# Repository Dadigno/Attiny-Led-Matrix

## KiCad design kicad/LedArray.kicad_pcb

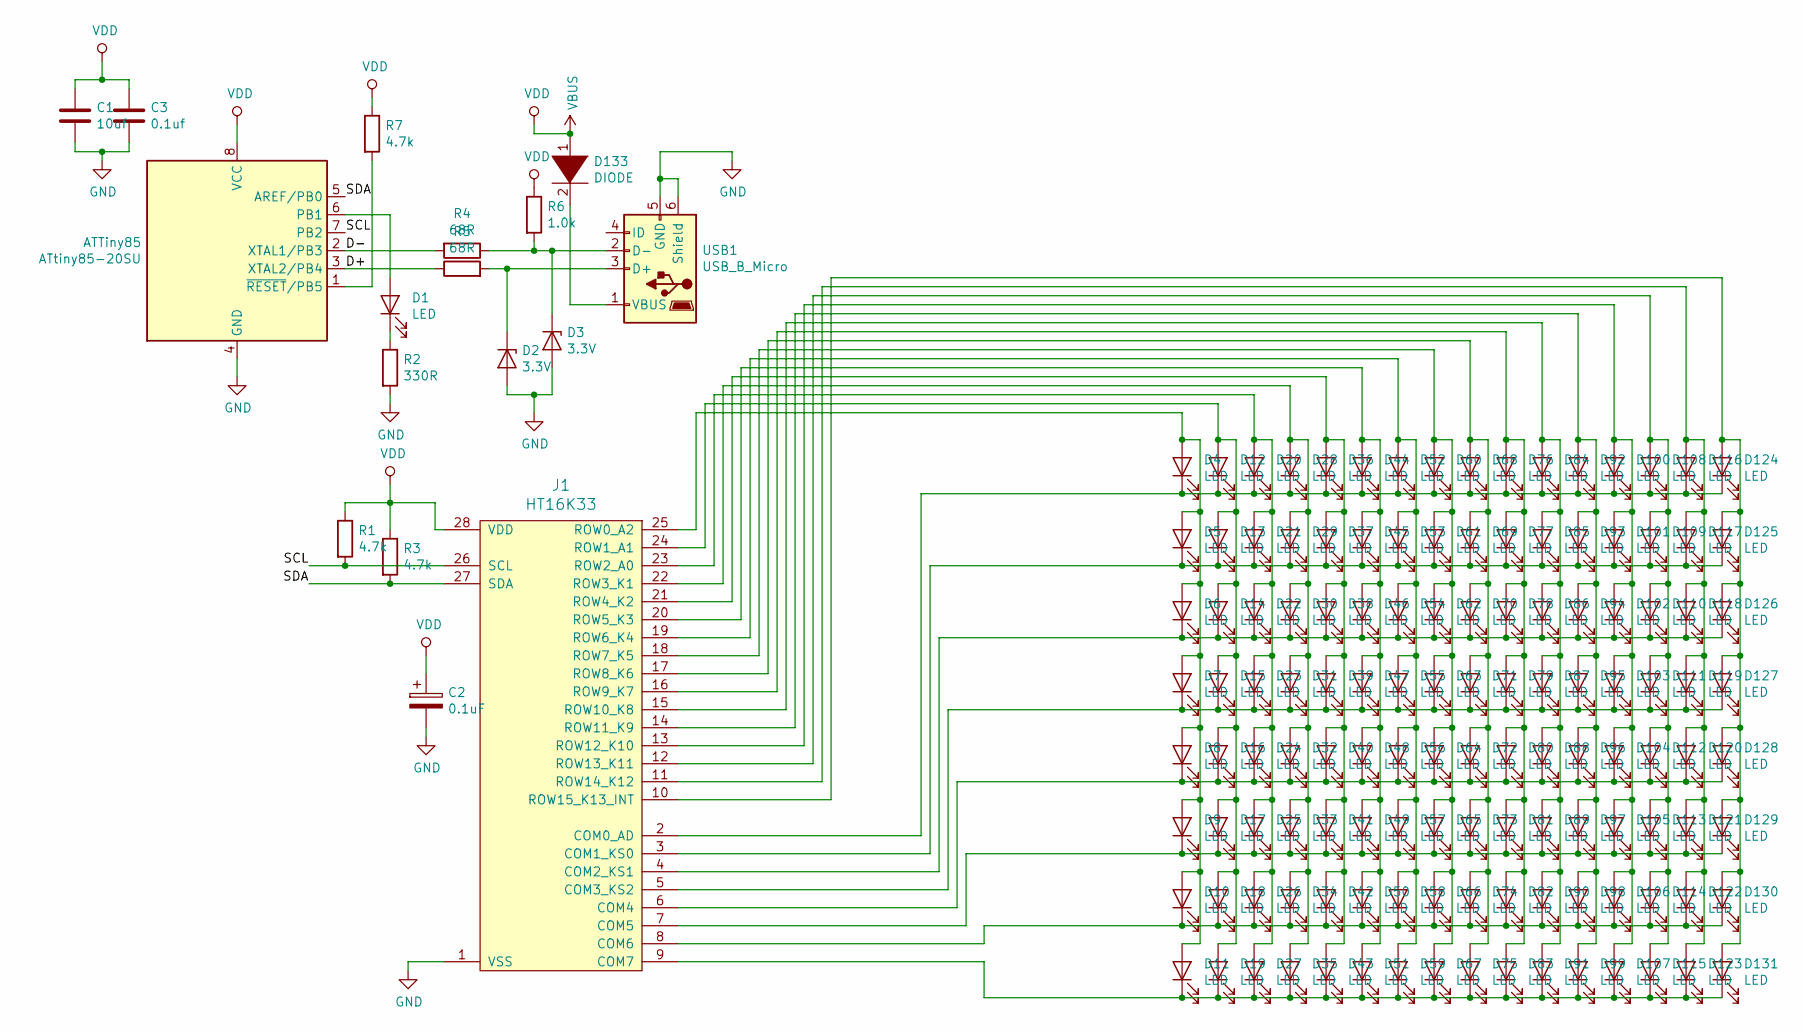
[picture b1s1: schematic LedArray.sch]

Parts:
ATTiny85: ATtiny85-20SU; SOIJ-8_5.3x5.3mm_P1.27mm
C1: 10uf; C_0805_2012Metric_Pad1.15x1.40mm_HandSolder
C2: 0.1uF; C_0805_2012Metric_Pad1.15x1.40mm_HandSolder
C3: 0.1uf; C_0805_2012Metric_Pad1.15x1.40mm_HandSolder
D1: LED; LED_0805_2012Metric_Pad1.15x1.40mm_HandSolder
D2, D3: 3.3V; D_SOD-523
D4, D5, D6, D7, D8, D9, D10, D11, D12, D13, D14, D15, D16, D17, D18, D19, D20, D21, D22, D23, D24, D25, D26, D27, D28, D29, D30, D31, D32, D33, D34, D35, D36, D37, D38, D39, D40, D41, D42, D43, D44, D45, D46, D47, D48, D49, D50, D51, D52, D53, D54, D55, D56, D57, D58, D59, D60, D61, D62, D63, D64, D65, D66, D67, D68, D69, D70, D71, D72, D73, D74, D75, D76, D77, D78, D79, D80, D81, D82, D83, D84, D85, D86, D87, D88, D89, D90, D91, D92, D93, D94, D95, D96, D97, D98, D99, D100, D101, D102, D103, D104, D105, D106, D107, D108, D109, D110, D111, D112, D113, D114, D115, D116, D117, D118, D119, D120, D121, D122, D123, D124, D125, D126, D127, D128, D129, D130, D131: LED; LED_0603_1608Metric_Pad1.05x0.95mm_HandSolder
D133: DIODE; D_1206_3216Metric_Pad1.42x1.75mm_HandSolder
J1: HT16K33; SOP-A-28_10.31_x17.9mm_P1.27
R1, R3, R7: 4.7k; R_0805_2012Metric_Pad1.15x1.40mm_HandSolder
R2: 330R; R_0805_2012Metric_Pad1.15x1.40mm_HandSolder
R4, R5: 68R; R_0805_2012Metric_Pad1.15x1.40mm_HandSolder
R6: 1.0k; R_0805_2012Metric_Pad1.15x1.40mm_HandSolder
USB1: USB_B_Micro; USB_Mini-B_Wuerth_65100516121_Horizontal

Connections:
/D+: ATTiny85.3 (XTAL2/PB4), R5.1
/D-: ATTiny85.2 (XTAL1/PB3), R4.2
/SCL: ATTiny85.7 (PB2), J1.26 (SCL), R1.2
/SDA: ATTiny85.5 (AREF/PB0), J1.27 (SDA), R3.2
GND: ATTiny85.4 (GND), C1.2, C2.2, C3.2, D2.2 (A), D3.2 (A), J1.1 (VSS), R2.2, USB1.5 (GND), USB1.6 (Shield)
unnamed: ATTiny85.1 (~RESET~/PB5), R7.2
unnamed: ATTiny85.6 (PB1), D1.2 (A)
unnamed: D1.1 (K), R2.1
unnamed: D2.1 (K), R5.2, USB1.3 (D+)
unnamed: D3.1 (K), R4.1, R6.2, USB1.2 (D-)
unnamed: D10.1 (K), D18.1 (K), D26.1 (K), D34.1 (K), D42.1 (K), D50.1 (K), D58.1 (K), D66.1 (K), D74.1 (K), D82.1 (K), D90.1 (K), D98.1 (K), D106.1 (K), D114.1 (K), D122.1 (K), D130.1 (K), J1.8 (COM6)
unnamed: D4.2 (A), D5.2 (A), D6.2 (A), D7.2 (A), D8.2 (A), D9.2 (A), D10.2 (A), D11.2 (A), J1.25 (ROW0_A2)
unnamed: D12.2 (A), D13.2 (A), D14.2 (A), D15.2 (A), D16.2 (A), D17.2 (A), D18.2 (A), D19.2 (A), J1.24 (ROW1_A1)
unnamed: D20.2 (A), D21.2 (A), D22.2 (A), D23.2 (A), D24.2 (A), D25.2 (A), D26.2 (A), D27.2 (A), J1.23 (ROW2_A0)
unnamed: D28.2 (A), D29.2 (A), D30.2 (A), D31.2 (A), D32.2 (A), D33.2 (A), D34.2 (A), D35.2 (A), J1.22 (ROW3_K1)
unnamed: D36.2 (A), D37.2 (A), D38.2 (A), D39.2 (A), D40.2 (A), D41.2 (A), D42.2 (A), D43.2 (A), J1.21 (ROW4_K2)
unnamed: D44.2 (A), D45.2 (A), D46.2 (A), D47.2 (A), D48.2 (A), D49.2 (A), D50.2 (A), D51.2 (A), J1.20 (ROW5_K3)
unnamed: D52.2 (A), D53.2 (A), D54.2 (A), D55.2 (A), D56.2 (A), D57.2 (A), D58.2 (A), D59.2 (A), J1.19 (ROW6_K4)
unnamed: D60.2 (A), D61.2 (A), D62.2 (A), D63.2 (A), D64.2 (A), D65.2 (A), D66.2 (A), D67.2 (A), J1.18 (ROW7_K5)
unnamed: D68.2 (A), D69.2 (A), D70.2 (A), D71.2 (A), D72.2 (A), D73.2 (A), D74.2 (A), D75.2 (A), J1.17 (ROW8_K6)
unnamed: D76.2 (A), D77.2 (A), D78.2 (A), D79.2 (A), D80.2 (A), D81.2 (A), D82.2 (A), D83.2 (A), J1.16 (ROW9_K7)
unnamed: D84.2 (A), D85.2 (A), D86.2 (A), D87.2 (A), D88.2 (A), D89.2 (A), D90.2 (A), D91.2 (A), J1.15 (ROW10_K8)
unnamed: D92.2 (A), D93.2 (A), D94.2 (A), D95.2 (A), D96.2 (A), D97.2 (A), D98.2 (A), D99.2 (A), J1.14 (ROW11_K9)
unnamed: D4.1 (K), D12.1 (K), D20.1 (K), D28.1 (K), D36.1 (K), D44.1 (K), D52.1 (K), D60.1 (K), D68.1 (K), D76.1 (K), D84.1 (K), D92.1 (K), D100.1 (K), D108.1 (K), D116.1 (K), D124.1 (K), J1.2 (COM0_AD)
unnamed: D100.2 (A), D101.2 (A), D102.2 (A), D103.2 (A), D104.2 (A), D105.2 (A), D106.2 (A), D107.2 (A), J1.13 (ROW12_K10)
unnamed: D5.1 (K), D13.1 (K), D21.1 (K), D29.1 (K), D37.1 (K), D45.1 (K), D53.1 (K), D61.1 (K), D69.1 (K), D77.1 (K), D85.1 (K), D93.1 (K), D101.1 (K), D109.1 (K), D117.1 (K), D125.1 (K), J1.3 (COM1_KS0)
unnamed: D6.1 (K), D14.1 (K), D22.1 (K), D30.1 (K), D38.1 (K), D46.1 (K), D54.1 (K), D62.1 (K), D70.1 (K), D78.1 (K), D86.1 (K), D94.1 (K), D102.1 (K), D110.1 (K), D118.1 (K), D126.1 (K), J1.4 (COM2_KS1)
unnamed: D7.1 (K), D15.1 (K), D23.1 (K), D31.1 (K), D39.1 (K), D47.1 (K), D55.1 (K), D63.1 (K), D71.1 (K), D79.1 (K), D87.1 (K), D95.1 (K), D103.1 (K), D111.1 (K), D119.1 (K), D127.1 (K), J1.5 (COM3_KS2)
unnamed: D8.1 (K), D16.1 (K), D24.1 (K), D32.1 (K), D40.1 (K), D48.1 (K), D56.1 (K), D64.1 (K), D72.1 (K), D80.1 (K), D88.1 (K), D96.1 (K), D104.1 (K), D112.1 (K), D120.1 (K), D128.1 (K), J1.6 (COM4)
unnamed: D9.1 (K), D17.1 (K), D25.1 (K), D33.1 (K), D41.1 (K), D49.1 (K), D57.1 (K), D65.1 (K), D73.1 (K), D81.1 (K), D89.1 (K), D97.1 (K), D105.1 (K), D113.1 (K), D121.1 (K), D129.1 (K), J1.7 (COM5)
unnamed: D11.1 (K), D19.1 (K), D27.1 (K), D35.1 (K), D43.1 (K), D51.1 (K), D59.1 (K), D67.1 (K), D75.1 (K), D83.1 (K), D91.1 (K), D99.1 (K), D107.1 (K), D115.1 (K), D123.1 (K), D131.1 (K), J1.9 (COM7)
unnamed: D108.2 (A), D109.2 (A), D110.2 (A), D111.2 (A), D112.2 (A), D113.2 (A), D114.2 (A), D115.2 (A), J1.12 (ROW13_K11)
unnamed: D116.2 (A), D117.2 (A), D118.2 (A), D119.2 (A), D120.2 (A), D121.2 (A), D122.2 (A), D123.2 (A), J1.11 (ROW14_K12)
unnamed: D124.2 (A), D125.2 (A), D126.2 (A), D127.2 (A), D128.2 (A), D129.2 (A), D130.2 (A), D131.2 (A), J1.10 (ROW15_K13_INT)
unnamed: D133.2 (A), USB1.1 (VBUS)
VBUS: ATTiny85.8 (VCC), C1.1, C2.1, C3.1, D133.1 (K), J1.28 (VDD), R1.1, R3.1, R6.1, R7.1

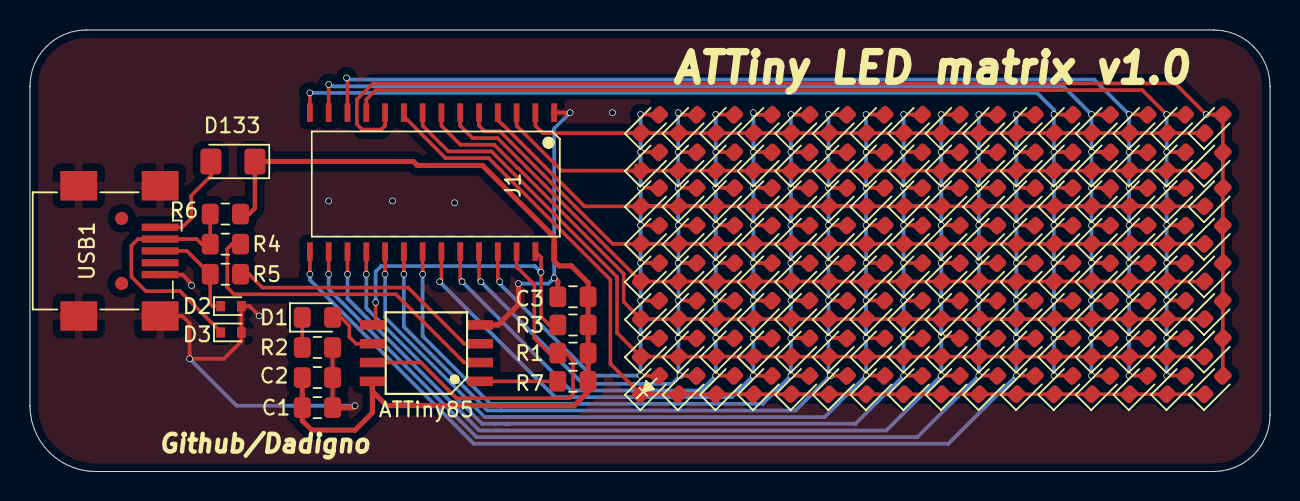
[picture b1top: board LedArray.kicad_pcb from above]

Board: 2 copper layers, 83.8 x 29.8 mm, 145 parts (0 on the bottom side), 36 nets.

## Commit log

2021-03-03 Add files
2021-03-03 add datasheets
2021-04-01 patched
2021-04-01 diode reversed
